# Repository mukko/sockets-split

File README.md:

# Sockets Split Keyboard

このデータで生産しても、一切の責任を負いません。  

# zinc keyboardを推奨しています

つくりがしっかりとしていて、価格も安く素敵なzincキーボードを推奨しています。  
https://booth.pm/ja/items/1076720

## 特徴

このキーボードは `左右対称配列`であり、 `スイッチソケット専用`、 `ProMicroスプリングピンヘッダ対応`をした 両手で`48キー`のキーボードです。 
あまり見かけないこの配列にまずはシンプルに入門できればよいと考え、またNext Let's splitとして作成しました。  
  
はんだ付けの難易度は、表面実装の部品があるため若干難しめと考えています。  
表面実装部品はソケットとダイオードです。それらのはんだ付けの練習キットとしてもいいかもしれません。  

ProMicroの結線はLet's split rev2に準拠しており、もしお使いの場合そのキーマップをそのまま利用することが可能です。  

## rev1.2, 1.3の諸注意
ケース、スイッチ組み立てページに記載しています。

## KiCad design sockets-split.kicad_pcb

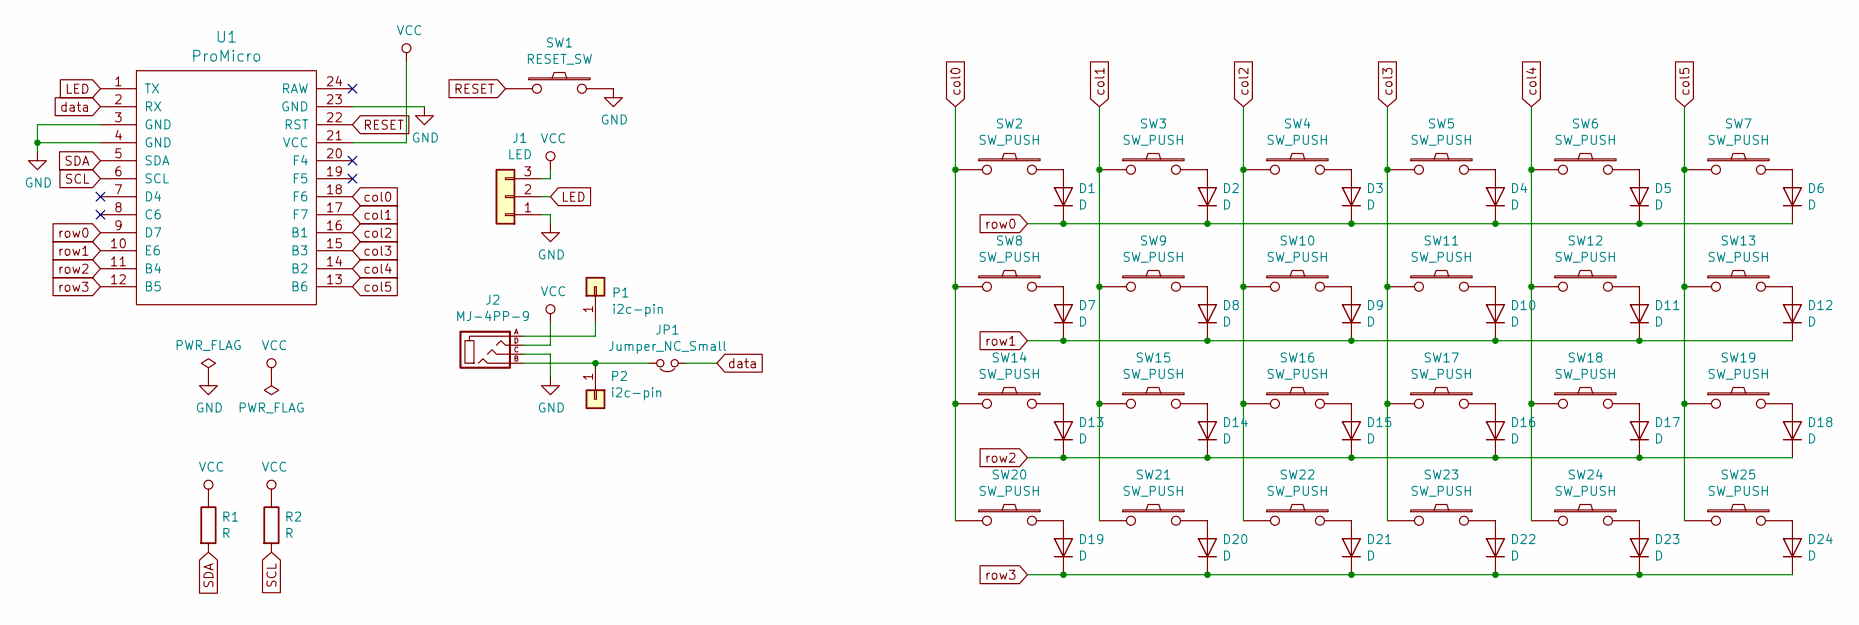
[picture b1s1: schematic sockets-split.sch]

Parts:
D1, D2, D3, D4, D5, D6, D7, D8, D9, D10, D11, D12, D13, D14, D15, D16, D17, D18, D19, D20, D21, D22, D23, D24: D; D3_TH_SMD
J1: LED; StripLED_THT
J2: MJ-4PP-9
JP1: Jumper_NC_Small; JPC2
P1, P2: i2c-pin; 1pin_conn
R1, R2: R
SW1: RESET_SW; ResetSW_4P
SW2, SW3, SW4, SW5, SW6, SW7, SW8, SW9, SW10, SW11, SW12, SW13, SW14, SW15, SW16, SW17, SW18, SW19, SW20, SW21, SW22, SW23, SW24, SW25: SW_PUSH; CherryMX_Hotswap
U1: ProMicro; ProMicro_v2_ura_pcb_for_sockets_split

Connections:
GND: J1.1, J2.C, SW1.2, U1.3 (GND), U1.4 (GND), U1.23 (GND)
LED: J1.2, U1.1 (TX)
unnamed: D1.2 (A), SW2.2
unnamed: D2.2 (A), SW3.2
unnamed: D3.2 (A), SW4.2
unnamed: D4.2 (A), SW5.2
unnamed: D5.2 (A), SW6.2
unnamed: D6.2 (A), SW7.2
unnamed: D7.2 (A), SW8.2
unnamed: D8.2 (A), SW9.2
unnamed: D9.2 (A), SW10.2
unnamed: D10.2 (A), SW11.2
unnamed: D11.2 (A), SW12.2
unnamed: D12.2 (A), SW13.2
unnamed: D13.2 (A), SW14.2
unnamed: D14.2 (A), SW15.2
unnamed: D15.2 (A), SW16.2
unnamed: D16.2 (A), SW17.2
unnamed: D17.2 (A), SW18.2
unnamed: D18.2 (A), SW19.2
unnamed: D19.2 (A), SW20.2
unnamed: D20.2 (A), SW21.2
unnamed: D21.2 (A), SW22.2
unnamed: D22.2 (A), SW23.2
unnamed: D23.2 (A), SW24.2
unnamed: D24.2 (A), SW25.2
unnamed: J2.A, P1.1
unnamed: J2.B, JP1.2, P2.1
RESET: SW1.1, U1.22 (RST)
SCL: R2.2, U1.6 (SCL)
SDA: R1.2, U1.5 (SDA)
VCC: J1.3, J2.D, R1.1, R2.1, U1.21 (VCC)
col0: SW2.1, SW8.1, SW14.1, SW20.1, U1.18 (F6)
col1: SW3.1, SW9.1, SW15.1, SW21.1, U1.17 (F7)
col2: SW4.1, SW10.1, SW16.1, SW22.1, U1.16 (B1)
col3: SW5.1, SW11.1, SW17.1, SW23.1, U1.15 (B3)
col4: SW6.1, SW12.1, SW18.1, SW24.1, U1.14 (B2)
col5: SW7.1, SW13.1, SW19.1, SW25.1, U1.13 (B6)
data: JP1.1, U1.2 (RX)
row0: D1.1 (K), D2.1 (K), D3.1 (K), D4.1 (K), D5.1 (K), D6.1 (K), U1.9 (D7)
row1: D7.1 (K), D8.1 (K), D9.1 (K), D10.1 (K), D11.1 (K), D12.1 (K), U1.10 (E6)
row2: D13.1 (K), D14.1 (K), D15.1 (K), D16.1 (K), D17.1 (K), D18.1 (K), U1.11 (B4)
row3: D19.1 (K), D20.1 (K), D21.1 (K), D22.1 (K), D23.1 (K), D24.1 (K), U1.12 (B5)

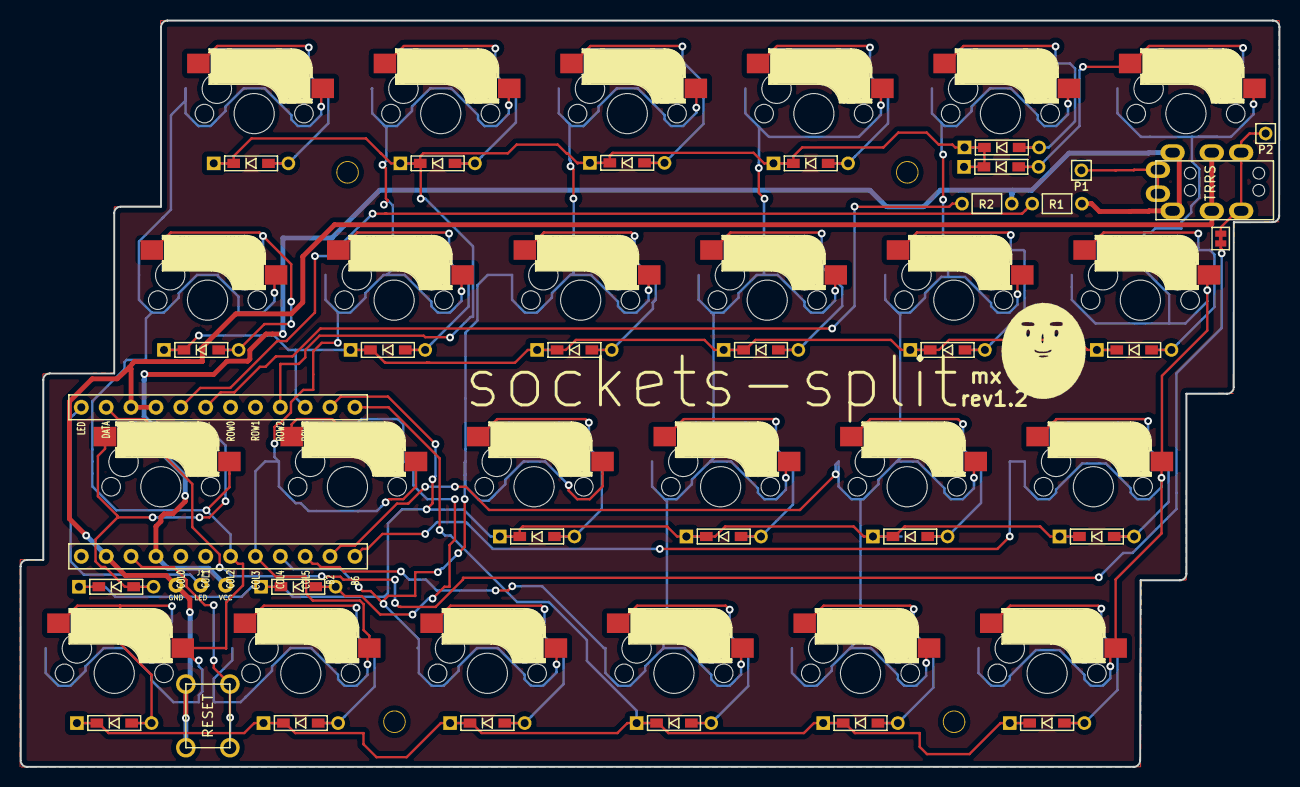
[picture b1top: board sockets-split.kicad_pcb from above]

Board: 2 copper layers, 128.5 x 76.2 mm, 61 parts (0 on the bottom side), 43 nets.

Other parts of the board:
Ref**: Val**; HOLE
Ref**#2, Ref**#3, Ref**#4: Val**; HOLE

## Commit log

2019-01-21 Add case
2019-01-21 Add LICENSE
2019-01-31 Fix JP to JPC
2019-02-10 Add LEDをTHTのフットプリントにした
2019-02-11 Fix ネットリスト修正
2019-02-18 再配線開始
2019-02-18 Add Underglow text & set diode
2019-02-19 [WIP]配線中
2019-02-19 キースイッチとpromicro配線できた
2019-03-05 Add GNDべた
2019-03-13 Add rev1
2019-04-08 Add key layout
2019-04-13 Fix module & draw case line
2019-04-15 Fix promicro, case
2019-06-16 Add gitbook
2019-08-12 Update ドキュメント
2019-08-12 Update document
2019-08-12 Fix SUMMARY
2019-08-14 Publish docs
2019-08-14 Fix delete published on gitbook
2019-08-14 Update docs
2019-09-04 Update LICENSE
2019-09-08 Fix promicro y + 2mm
2019-11-02 Add bottom plate
2019-11-24 Add solder layer & Fix document
2019-11-24 Update docs]
2019-12-01 add docs images, fix pcb
2019-12-01 fix filetype
2019-12-01 add image
2019-12-04 一発で生産できなかったので、pcbの修正
2019-12-05 穴を修正してみた
2020-01-07 promicroを変更
2020-01-12 Add GNDベタ
